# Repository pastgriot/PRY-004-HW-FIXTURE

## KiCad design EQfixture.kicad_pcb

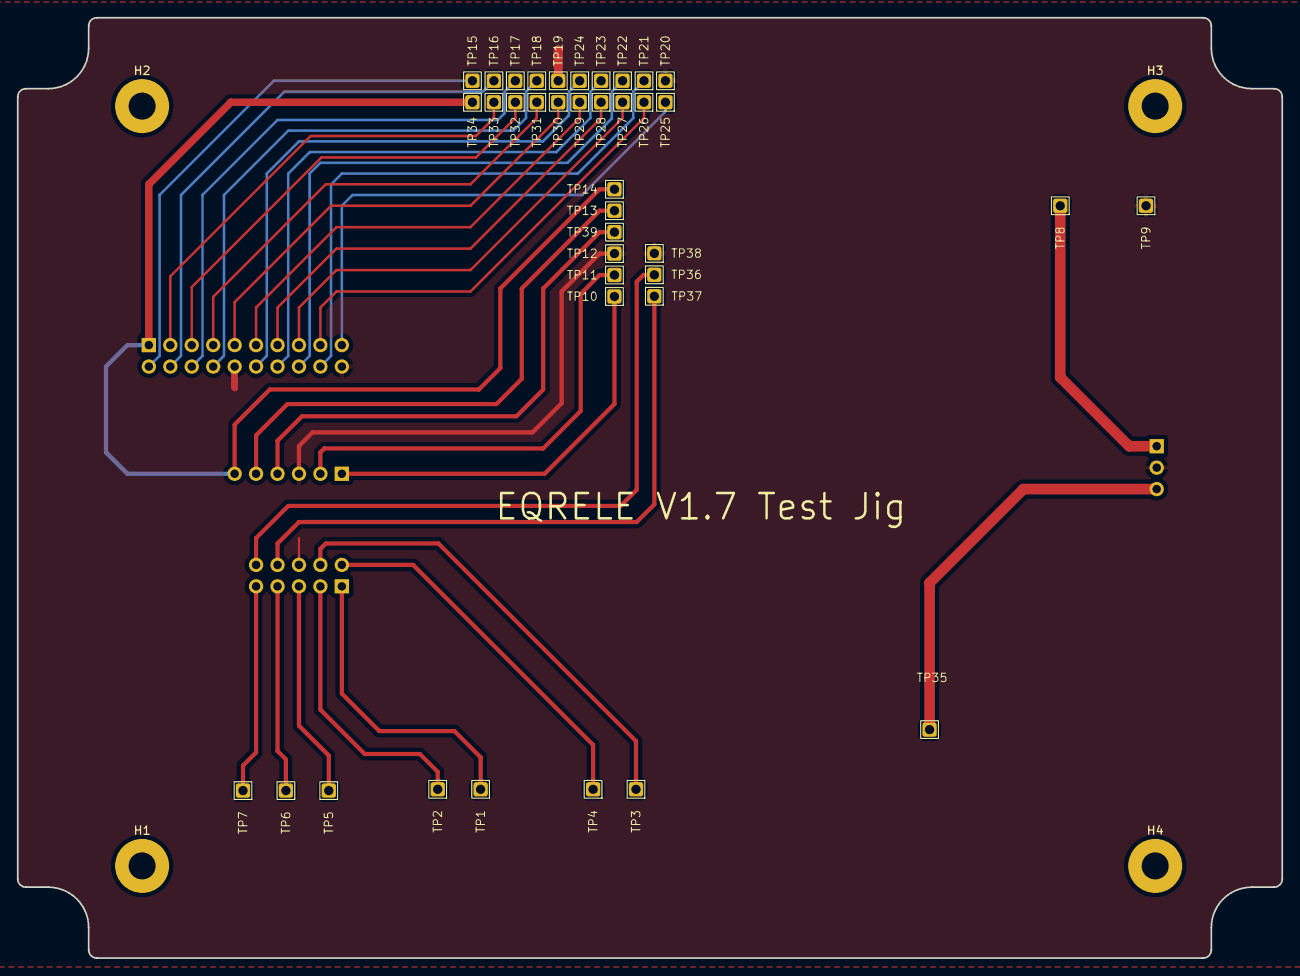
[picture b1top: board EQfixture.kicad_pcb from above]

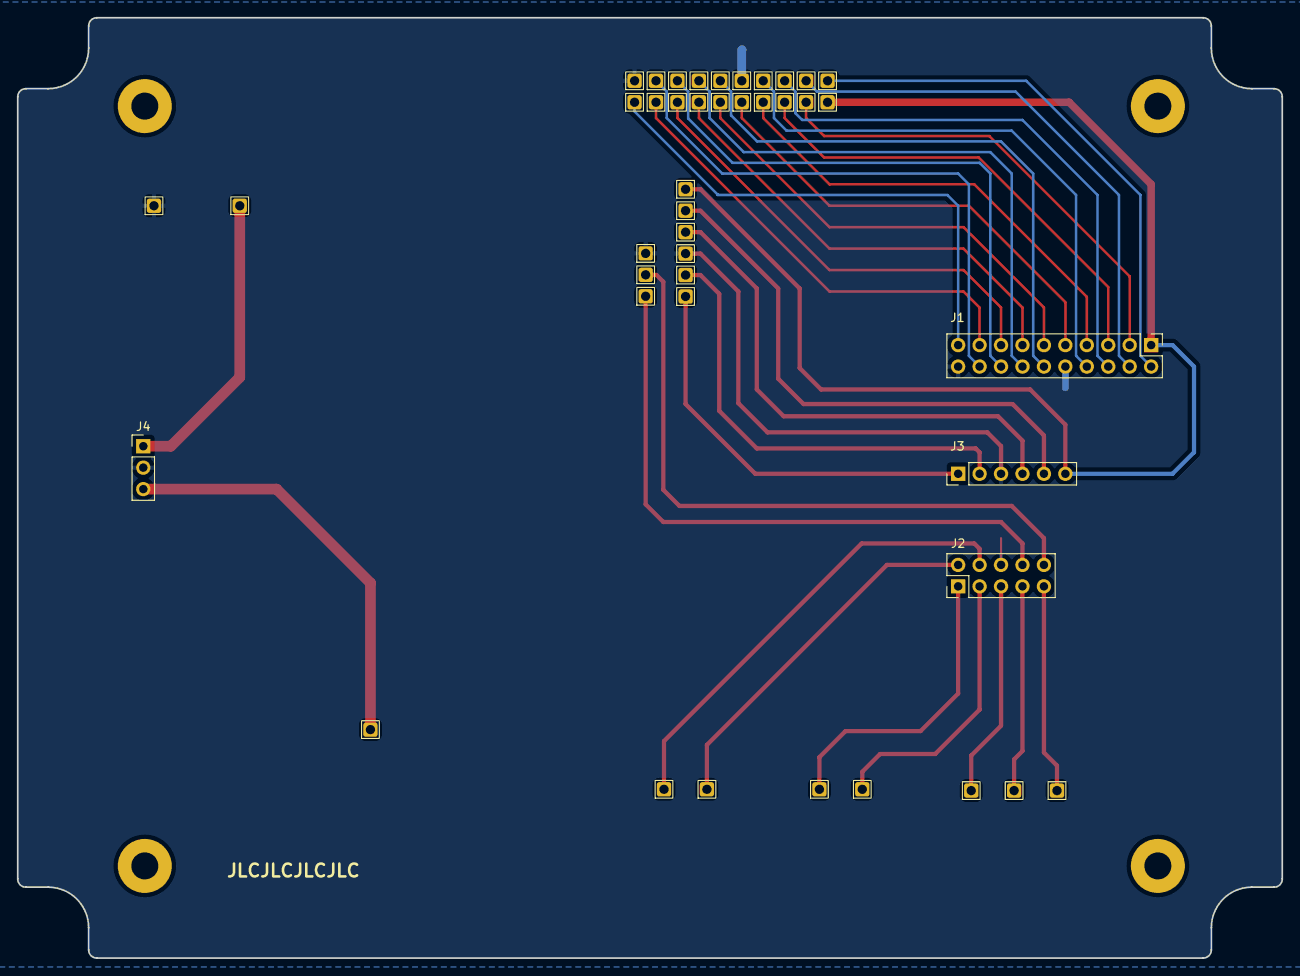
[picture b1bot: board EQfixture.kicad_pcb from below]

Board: 2 copper layers, 149.8 x 111.4 mm, 47 parts (4 on the bottom side), 34 nets.

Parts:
H1, H2, H3, H4: M3; MountingHole_3.2mm_M3_Pad
J1: Conn_02x10_Top_Bottom; PinHeader_2x10_P2.54mm_Vertical
J2: Conn_02x05_Top_Bottom; PinHeader_2x05_P2.54mm_Vertical
J3: Conn_01x06; PinHeader_1x06_P2.54mm_Vertical
J4: Conn_01x03; PinHeader_1x03_P2.54mm_Vertical
TP1: R_TST; TestPoint-TH-Square-1mmHole
TP2: R_TST_G; TestPoint-TH-Square-1mmHole
TP3: R_RST; TestPoint-TH-Square-1mmHole
TP4: R_RST_G; TestPoint-TH-Square-1mmHole
TP5: R_NC; TestPoint-TH-Square-1mmHole
TP6: R_COM; TestPoint-TH-Square-1mmHole
TP7: R_NA; TestPoint-TH-Square-1mmHole
TP8: 5VCC; TestPoint-TH-Square-1mmHole
TP9, TP12, TP19, TP20, TP38: GND; TestPoint-TH-Square-1mmHole
TP10: SWO; TestPoint-TH-Square-1mmHole
TP11: NRST; TestPoint-TH-Square-1mmHole
TP13: SWCLK; TestPoint-TH-Square-1mmHole
TP14, TP34: 3V3; TestPoint-TH-Square-1mmHole
TP15: I2C_SDA; TestPoint-TH-Square-1mmHole
TP16: ~{LED_BAT_OK}; TestPoint-TH-Square-1mmHole
TP17: ~{LED_FAIL}; TestPoint-TH-Square-1mmHole
TP18: ~{LED_TRIGGER}; TestPoint-TH-Square-1mmHole
TP21: LED_BAT_DONE; TestPoint-TH-Square-1mmHole
TP22: SW_UP; TestPoint-TH-Square-1mmHole
TP23: SW_TST_EVENT; TestPoint-TH-Square-1mmHole
TP24: SW_RST_EVENT; TestPoint-TH-Square-1mmHole
TP25: LED_BAT_CHRG; TestPoint-TH-Square-1mmHole
TP26: SW_DOWN; TestPoint-TH-Square-1mmHole
TP27: SW_ENTER; TestPoint-TH-Square-1mmHole
TP28: SW_EXIT; TestPoint-TH-Square-1mmHole
TP29: LED_RUNNING; TestPoint-TH-Square-1mmHole
TP30: LED_TRIGGER; TestPoint-TH-Square-1mmHole
TP31: LED_FAIL; TestPoint-TH-Square-1mmHole
TP32: LED_STANDBY; TestPoint-TH-Square-1mmHole
TP33: I2C_SCL; TestPoint-TH-Square-1mmHole
TP35: VCC_BATT; TestPoint-TH-Square-1mmHole
TP36: RX; TestPoint-TH-Square-1mmHole
TP37: TX; TestPoint-TH-Square-1mmHole
TP39: SWDIO; TestPoint-TH-Square-1mmHole

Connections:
+3V3: J1.1, J3.6, TP14.1, TP34.1
/I2C1_SCL: J1.3, TP33.1
/I2C1_SDA: J1.2, TP15.1
/LED_BAT_CHRG: J1.19, TP25.1
/LED_BAT_DONE: J1.18, TP21.1
/LED_FAIL: J1.7, TP31.1
/LED_STANDBY: J1.5, TP32.1
/LED_TRIGGER: J1.9, TP30.1
/MCU_RUNNING: J1.11, TP29.1
/SW_DOWN: J1.17, TP26.1
/SW_ENTER: J1.15, TP27.1
/SW_EXIT: J1.13, TP28.1
/SW_RST_EVENT: J1.12, TP24.1
/SW_TST_EVENT: J1.14, TP23.1
/SW_UP: J1.16, TP22.1
/~LED_BAT_OK: J1.4, TP16.1
/~LED_FAIL: J1.6, TP17.1
/~LED_TRIGGER: J1.8, TP18.1
GND: J1.10, J1.20, J2.6, J3.3, J4.2, TP9.1, TP12.1, TP19.1, TP20.1, TP38.1
unnamed: J2.1, TP1.1
unnamed: J2.2, TP4.1
unnamed: J2.3, TP2.1
unnamed: J2.4, TP3.1
unnamed: J2.5, TP5.1
unnamed: J2.7, TP6.1
unnamed: J2.8, TP37.1
unnamed: J2.9, TP7.1
unnamed: J2.10, TP36.1
unnamed: J3.1, TP10.1
unnamed: J3.2, TP11.1
unnamed: J3.4, TP39.1
unnamed: J3.5, TP13.1
unnamed: J4.1, TP8.1
unnamed: J4.3, TP35.1

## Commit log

2023-09-08 first upload
2023-09-08 defining holes
2023-09-14 pogos added
2023-09-18 done + gerber added
